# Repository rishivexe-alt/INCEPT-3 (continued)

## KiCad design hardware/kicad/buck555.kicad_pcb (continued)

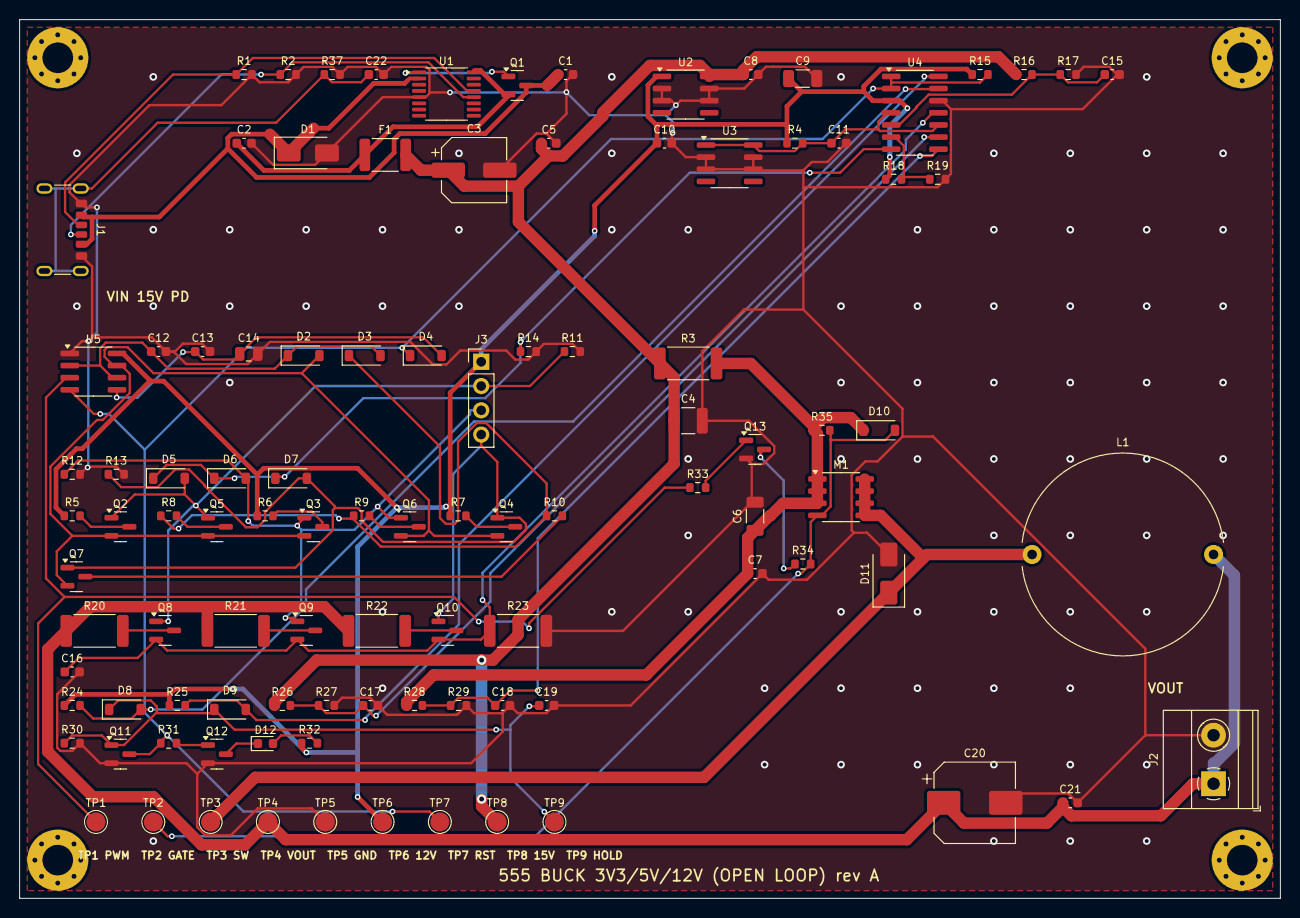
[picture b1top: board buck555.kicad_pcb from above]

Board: 2 copper layers, 132.0 x 92.0 mm, 107 parts (0 on the bottom side), 46 nets.

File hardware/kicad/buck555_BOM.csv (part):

Qty,References,Value,Footprint,Manufacturer,MPN,Description,MPN status
1,J1,USB-C PD in,Connector_USB:USB_C_Receptacle_GCT_USB4125-xx-x_6P_TopMnt_Horizontal,GCT,USB4125-GF-A,USB-C power-only 6-pin receptacle,generic/from memory - verify before ordering
1,R1,5.1k,Resistor_SMD:R_0603_1608Metric,Yageo,RC0603FR-075K1L,"CC1 Rd (per IP2721 datasheet figure - verify, see risks)",generic/from memory - verify before ordering
1,R2,5.1k,Resistor_SMD:R_0603_1608Metric,Yageo,RC0603FR-075K1L,"CC2 Rd (per IP2721 datasheet figure - verify, see risks)",generic/from memory - verify before ordering
1,R37,1M,Resistor_SMD:R_0603_1608Metric,Yageo,RC0603FR-071ML,USB shield bleed,generic/from memory - verify before ordering
1,C22,4.7n,Capacitor_SMD:C_0603_1608Metric,Yageo,CC0603KRX7R9BB472,USB shield 50 V X7R,generic/from memory - verify before ordering
1,U1,IP2721,Package_SO:TSSOP-16_4.4x5mm_P0.65mm,Injoinic,IP2721,"USB-C PD sink (trigger), SEL floating = 15 V request",checked against datasheet
1,Q1,AO3400A,Package_TO_SOT_SMD:SOT-23,Alpha & Omega,AO3400A,PD path NMOS 30 V 5.7 A,generic/from memory - verify before ordering
1,C1,1u,Capacitor_SMD:C_0603_1608Metric,Murata,GRM188R71H105KA61D,IP2721 VIN cap 50 V X7R,generic/from memory - verify before ordering
1,C2,1u,Capacitor_SMD:C_0603_1608Metric,Murata,GRM188R71H105KA61D,IP2721 VBUS cap 50 V X7R,generic/from memory - verify before ordering
1,D1,SMAJ15A,Diode_SMD:D_SMA,Littelfuse,SMAJ15A,"TVS 15 V standoff, 24.4 V clamp",generic/from memory - verify before ordering
1,F1,3A hold,Fuse:Fuse_1812_4532Metric,Bourns,MF-MSMF300/16X-2,"Resettable fuse 3 A hold, >=16 V (verify rating)",generic/from memory - verify before ordering
1,C3,47u,Capacitor_SMD:CP_Elec_6.3x7.7,Panasonic,EEE-FK1E470P,Input bulk 25 V electrolytic,generic/from memory - verify before ordering
1,C4,10u,Capacitor_SMD:C_1210_3225Metric,Murata,GRM32ER71E106KA12L,Input ceramic 25 V X7R,generic/from memory - verify before ordering
1,C5,100n,Capacitor_SMD:C_0603_1608Metric,Yageo,CC0603KRX7R9BB104,Input HF decoupling 50 V X7R,generic/from memory - verify before ordering
1,R3,0.15,Resistor_SMD:R_2512_6332Metric,Bourns,CRM2512-FX-R150ELF,Current-sense resistor 1 W 1%,generic/from memory - verify before ordering
1,C6,2.2u,Capacitor_SMD:C_1206_3216Metric,Murata,GRM31CR71E225KA73L,Switch-node input cap 25 V X7R,generic/from memory - verify before ordering
1,C7,100n,Capacitor_SMD:C_0603_1608Metric,Yageo,CC0603KRX7R9BB104,Switch HF cap,generic/from memory - verify before ordering
1,U2,L78L12,Package_SO:SOIC-8_3.9x4.9mm_P1.27mm,STMicroelectronics,L78L12ACD13TR,12 V timer/logic rail (555 max supply 15 V),generic/from memory - verify before ordering
5,C8 C10 C11 C16 C21,100n,Capacitor_SMD:C_0603_1608Metric,Yageo,CC0603KRX7R9BB104,Capacitor 100n,generic/from memory - verify before ordering
1,C9,10u,Capacitor_SMD:C_1206_3216Metric,Murata,GRM31CR71E106KA12L,12 V rail 25 V X7R,generic/from memory - verify before ordering
1,U3,TL431,Package_SO:SOIC-8_3.9x4.9mm_P1.27mm,Texas Instruments,TL431AIDR,2.495 V reference (K tied to REF),generic/from memory - verify before ordering
1,R4,3.9k,Resistor_SMD:R_0603_1608Metric,Yageo,RC0603FR-073K9L,TL431 bias ~2.4 mA,generic/from memory - verify before ordering
1,U4,LM339,Package_SO:SOIC-14_3.9x8.7mm_P1.27mm,Texas Instruments,LM339DR,"Quad comparator, open-collector (UV, selector-valid, OV, OC)",generic/from memory - verify before ordering
1,R15,100k,Resistor_SMD:R_0603_1608Metric,Yageo,RC0603FR-07100KL,RESET pull-up (OR-wired interlock bus),generic/from memory - verify before ordering
1,R16,100k,Resistor_SMD:R_0603_1608Metric,Yageo,RT0603BRD07100KL,UV divider top 0.1%,generic/from memory - verify before ordering
1,R17,22.6k,Resistor_SMD:R_0603_1608Metric,Yageo,RT0603BRD0722K6L,UV divider bottom 0.1%,generic/from memory - verify before ordering
1,C15,10n,Capacitor_SMD:C_0603_1608Metric,Yageo,CC0603KRX7R9BB103,Capacitor 10n,generic/from memory - verify before ordering
2,R18 R19,10k,Resistor_SMD:R_0603_1608Metric,Yageo,RC0603FR-0710KL,Resistor 10k 1%,generic/from memory - verify before ordering
1,U5,TLC555,Package_SO:SOIC-8_3.9x4.9mm_P1.27mm,Texas Instruments,TLC555CDR,CMOS 555 astable PWM generator (2-15 V),checked against datasheet
1,C12,4.7n,Capacitor_SMD:C_0603_1608Metric,Murata,GCM1885C1H472JA16D,Timing cap C0G/NP0 50 V,generic/from memory - verify before ordering
1,C13,10n,Capacitor_SMD:C_0603_1608Metric,Yageo,CC0603KRX7R9BB103,CONTROL pin 10 nF,generic/from memory - verify before ordering
1,C14,2.2u,Capacitor_SMD:C_0805_2012Metric,Murata,GRM21BR71A225KA01L,Soft-start cap 10 V X7R,generic/from memory - verify before ordering
1,D2,1N4148W,Diode_SMD:D_SOD-123,Diodes Inc.,1N4148W-7-F,Charge-steering diode (X -> TC),generic/from memory - verify before ordering
1,D3,1N4148W,Diode_SMD:D_SOD-123,Diodes Inc.,1N4148W-7-F,Discharge-steering diode (TC -> Y),generic/from memory - verify before ordering
1,D4,1N4148W,Diode_SMD:D_SOD-123,Diodes Inc.,1N4148W-7-F,Soft-start reset diode (CTRL -> RST),generic/from memory - verify before ordering
1,R5,953,Resistor_SMD:R_0603_1608Metric,Yageo,RC0603FR-07953RL,RA mode 1,generic/from memory - verify before ordering
1,Q2,2N7002,Package_TO_SOT_SMD:SOT-23,onsemi,2N7002,RA select mode 1,generic/from memory - verify before ordering
1,R8,9.76k,Resistor_SMD:R_0603_1608Metric,Yageo,RC0603FR-079K76L,RB mode 1,generic/from memory - verify before ordering
1,Q5,2N7002,Package_TO_SOT_SMD:SOT-23,onsemi,2N7002,RB select mode 1,generic/from memory - verify before ordering
1,R6,2.21k,Resistor_SMD:R_0603_1608Metric,Yageo,RC0603FR-072K21L,RA mode 2,generic/from memory - verify before ordering
1,Q3,2N7002,Package_TO_SOT_SMD:SOT-23,onsemi,2N7002,RA select mode 2,generic/from memory - verify before ordering
1,R9,8.66k,Resistor_SMD:R_0603_1608Metric,Yageo,RC0603FR-078K66L,RB mode 2,generic/from memory - verify before ordering
1,Q6,2N7002,Package_TO_SOT_SMD:SOT-23,onsemi,2N7002,RB select mode 2,generic/from memory - verify before ordering
1,R7,7.5k,Resistor_SMD:R_0603_1608Metric,Yageo,RC0603FR-077K5L,RA mode 3,generic/from memory - verify before ordering
1,Q4,2N7002,Package_TO_SOT_SMD:SOT-23,onsemi,2N7002,RA select mode 3,generic/from memory - verify before ordering
1,R10,3.4k,Resistor_SMD:R_0603_1608Metric,Yageo,RC0603FR-073K4L,RB mode 3,generic/from memory - verify before ordering
1,Q7,2N7002,Package_TO_SOT_SMD:SOT-23,onsemi,2N7002,RB select mode 3,generic/from memory - verify before ordering
1,J3,ROTARY,Connector_PinHeader_2.54mm:PinHeader_1x04_P2.54mm_Vertical,Generic,2.54mm 1x4 header,"Off-board rotary switch: 1 pole x 3 pos, NON-shorting (break-before-make)","spec only, no verified MPN"
1,R11,100k,Resistor_SMD:R_0603_1608Metric,Yageo,RC0603FR-07100KL,M1 pull-down,generic/from memory - verify before ordering
1,R12,100k,Resistor_SMD:R_0603_1608Metric,Yageo,RC0603FR-07100KL,M2 pull-down,generic/from memory - verify before ordering
1,R13,100k,Resistor_SMD:R_0603_1608Metric,Yageo,RC0603FR-07100KL,M3 pull-down,generic/from memory - verify before ordering
3,D5 D6 D7,1N4148W,Diode_SMD:D_SOD-123,Diodes Inc.,1N4148W-7-F,Selector-valid OR diode,generic/from memory - verify before ordering
1,R14,100k,Resistor_SMD:R_0603_1608Metric,Yageo,RC0603FR-07100KL,VAL pull-down,generic/from memory - verify before ordering
1,R20,18.2,Resistor_SMD:R_2512_6332Metric,Yageo,RC2512FR-0718R2L,Preload/OV-sense top resistor mode 1 (1 W),generic/from memory - verify before ordering
1,Q8,2N7002,Package_TO_SOT_SMD:SOT-23,onsemi,2N7002,Preload/OV string select mode 1,generic/from memory - verify before ordering
1,R21,44.2,Resistor_SMD:R_2512_6332Metric,Yageo,RC2512FR-0744R2L,Preload/OV-sense top resistor mode 2 (1 W),generic/from memory - verify before ordering
1,Q9,2N7002,Package_TO_SOT_SMD:SOT-23,onsemi,2N7002,Preload/OV string select mode 2,generic/from memory - verify before ordering
1,R22,147,Resistor_SMD:R_2512_6332Metric,Yageo,RC2512FR-07147RL,Preload/OV-sense top resistor mode 3 (1 W),generic/from memory - verify before ordering
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
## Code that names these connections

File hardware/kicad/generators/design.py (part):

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# ----------------------------------------------------------------- A: input / PD
S='A'
add('J1','Connector:USB_C_Receptacle_PowerOnly_6P','USB-C PD in','Connector_USB:USB_C_Receptacle_GCT_USB4125-xx-x_6P_TopMnt_Horizontal',
    {'A12':'GND','B12':'GND','A9':'VBUS','B9':'VBUS','A5':'CC1','B5':'CC2','S1':'SHIELD'},S,'GCT','USB4125-GF-A','USB-C power-only 6-pin receptacle',vf='gen')
R('R1','5.1k','CC1','GND',S,desc='CC1 Rd (per IP2721 datasheet figure - verify, see risks)',mpn='RC0603FR-075K1L',mfr='Yageo')
R('R2','5.1k','CC2','GND',S,desc='CC2 Rd (per IP2721 datasheet figure - verify, see risks)',mpn='RC0603FR-075K1L',mfr='Yageo')
R('R37','1M','SHIELD','GND',S,desc='USB shield bleed',mpn='RC0603FR-071ML',mfr='Yageo')
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add('U5','Timer:TLC555xD','TLC555',SOIC8,{'1':'GND','8':'+12V','2':'TC','3':'OUT555','4':'RST','5':'CTRL','6':'TC','7':'X'},S,
    'Texas Instruments','TLC555CDR','CMOS 555 astable PWM generator (2-15 V)',vf='ds')
C('C12','4.7n','TC','GND',S,mpn='GCM1885C1H472JA16D',mfr='Murata',desc='Timing cap C0G/NP0 50 V')
C('C13','10n','CTRL','GND',S,mpn='CC0603KRX7R9BB103',mfr='Yageo',desc='CONTROL pin 10 nF')
C('C14','2.2u','CTRL','GND',S,fp=C0805,mpn='GRM21BR71A225KA01L',mfr='Murata',desc='Soft-start cap 10 V X7R')
DD('D2','TC','X',S,desc='Charge-steering diode (X -> TC)')
DD('D3','Y','TC',S,desc='Discharge-steering diode (TC -> Y)')
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R('R34','470','GD','GATE',S,mpn='RC0603FR-07470RL',mfr='Yageo',desc='Gate series resistor (limits clamp current)')
R('R35','1k','VSRC','GATE',S,mpn='RC0603FR-071KL',mfr='Yageo',desc='Gate pull-up R7')
add('D10','Device:D_Zener','12V',SOD123,{'1':'VSRC','2':'GATE'},S,'Diodes Inc.','MMSZ5242B-7-F','Gate-source clamp 12 V (FDS4435A VGS max 20 V)',vf='gen')
add('M1','buck555:FDS4435A','FDS4435A',SOIC8,{'1':'VSRC','2':'VSRC','3':'VSRC','4':'GATE','5':'SW','6':'SW','7':'SW','8':'SW'},S,'onsemi','FDS4435A','P-MOSFET -30 V -8.8 A 20 mohm SO-8 (verify pinout vs datasheet drawing)',vf='ds')
add('D11','Diode:SS34','SS34',SMA,{'1':'SW','2':'GND'},S,'Vishay','SS34-E3/57T','Schottky 40 V 3 A freewheel diode',vf='gen')
add('L1','Device:L','1mH','Inductor_THT:L_Radial_D21.0mm_P19.00mm',{'1':'SW','2':'VOUT'},S,'','','1 mH, Isat >= 4.5 A (-30% L), Irms >= 2 A, DCR <= 0.12 ohm. NO MPN CHOSEN - see notes',vf='spec')
C('C20','220u','VOUT','GND',S,fp=CEL8,pol=True,mpn='EEE-FK1E221P',mfr='Panasonic',desc='Output bulk 25 V low-ESR (check ripple current)')
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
